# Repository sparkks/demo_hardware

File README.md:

# demo_hardware
Simple 78XX voltage regulator schematic and PCB board created using EAGLE 7.0.3
just temporary - for github testing purposes with schematic and PCB files

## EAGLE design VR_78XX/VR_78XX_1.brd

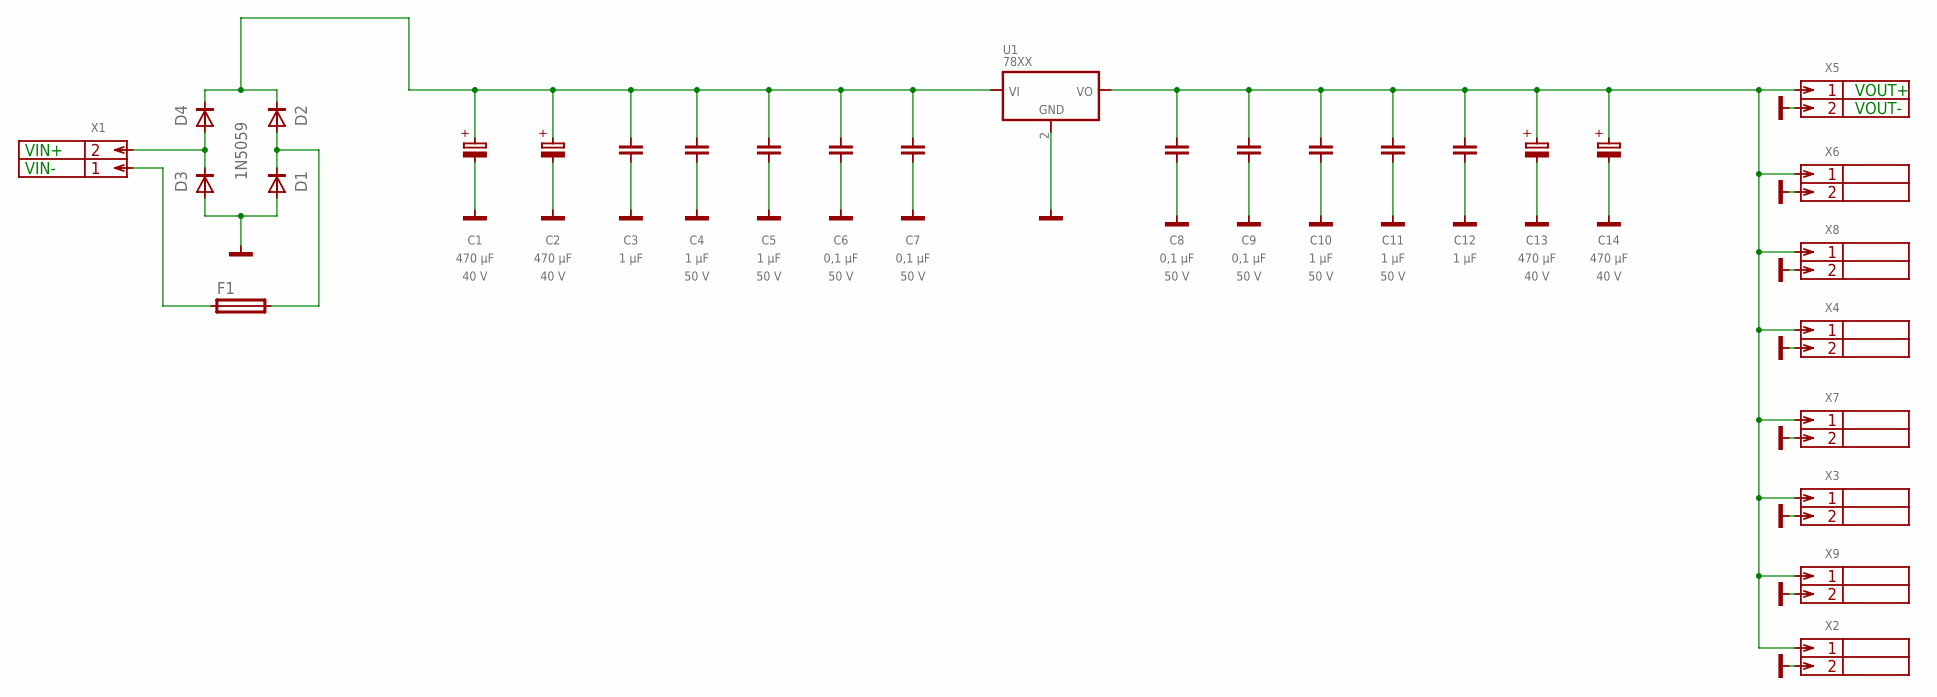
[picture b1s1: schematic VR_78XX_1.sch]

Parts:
C1, C2, C13, C14: 470 µF; AHT10-30C; VOLTAGE 40 V
C3, C12: 1 µF; 1
C4, C5, C10, C11: 1 µF; C050-025X075
C6, C7, C8, C9: 0,1 µF; C050-025X075
D1, D2, D3, D4: 1N5059; DO204-10
F1: GSH15
U1: 78XX; TO220H
X1: AK100V5; AK100-2V
X2, X3, X4, X5, X6, X7, X8, X9: MTA02-100; 10X02MTA

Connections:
GND: C1.-, C2.-, C3.2, C4.2, C5.2, C6.2, C7.2, C8.2, C9.2, C10.2, C11.2, C12.2, C13.-, C14.-, D1.A, D3.A, U1.2 (GND), X2.2, X3.2, X4.2, X5.2, X6.2, X7.2, X8.2, X9.2
unnamed: D3.C, D4.A, X1.P$2 (2)
unnamed: D1.C, D2.A, F1.2
unnamed: F1.1, X1.P$1 (1)
VIN+: C1.+, C2.+, C3.1, C4.1, C5.1, C6.1, C7.1, D2.C, D4.C, U1.1 (VI)
VOUT+: C8.1, C9.1, C10.1, C11.1, C12.1, C13.+, C14.+, U1.3 (VO), X2.1, X3.1, X4.1, X5.1, X6.1, X7.1, X8.1, X9.1

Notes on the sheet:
VIN+
VIN-
VOUT+
VOUT-

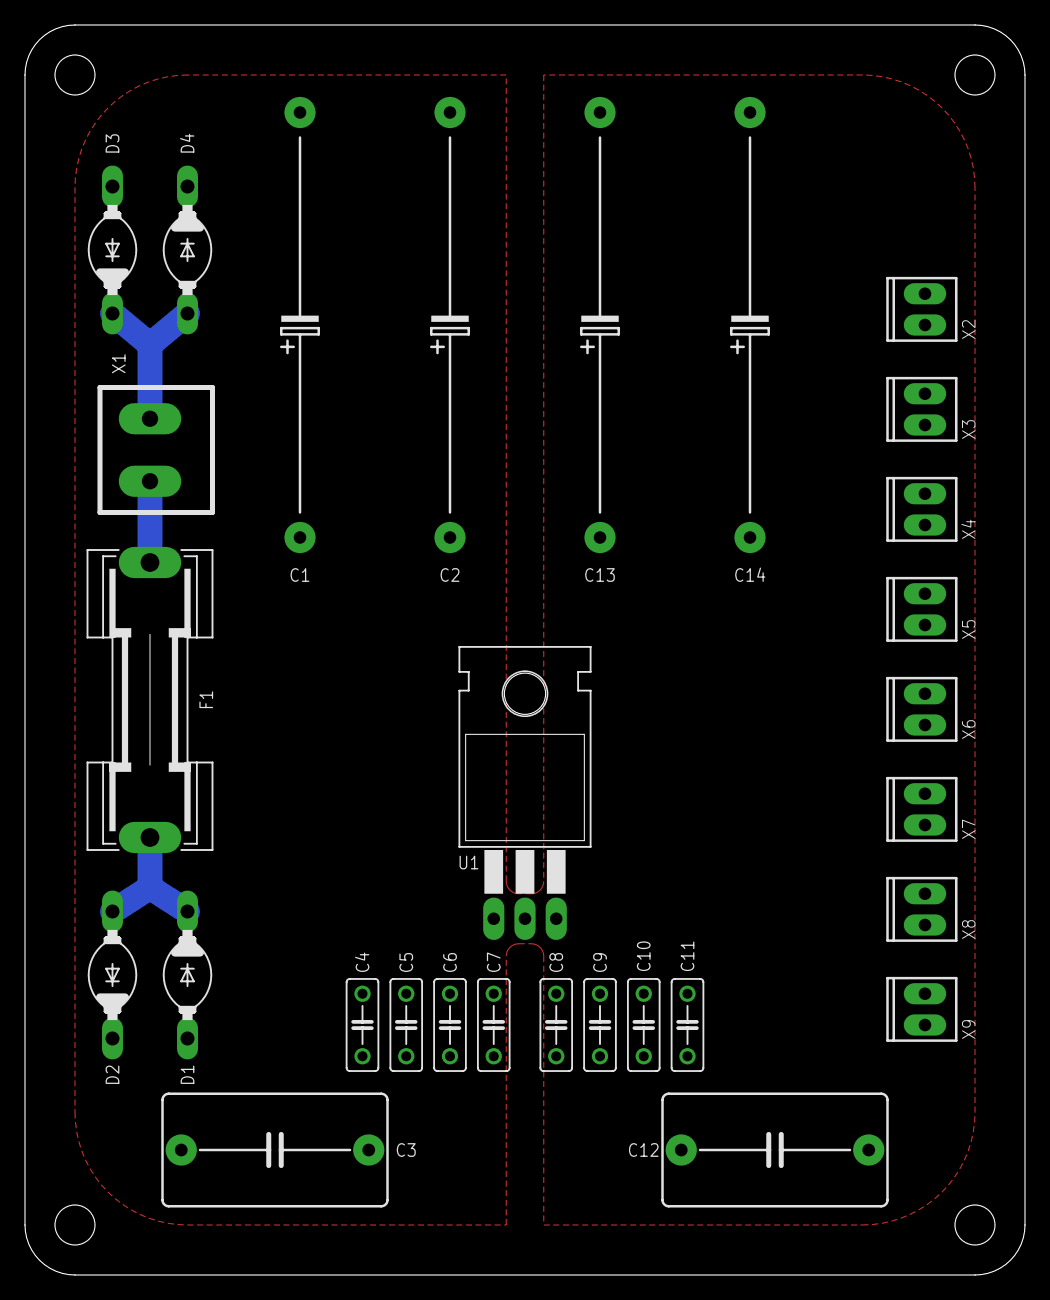
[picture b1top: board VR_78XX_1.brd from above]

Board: 2 copper layers, 80.0 x 100.0 mm, 34 parts (0 on the bottom side), 6 nets.

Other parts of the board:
U$1, U$2, U$3, U$4: KRASTAI3MM
U$6: 100X80PCB

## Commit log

2018-03-25 voltage regulator initial schematic and pcb files
2018-03-25 deleted film capacitors
2018-03-25 edited readme
2018-03-25 placed files to directory
2018-03-25 corection
2018-03-25 layout, caps
    cleaned layout a little bit, added ceramic bypass capacitors.
2018-03-25 layout, caps
    cleaned layout a little bit, added ceramic bypass caps.
2018-03-25 deleted unecessary temp files
2018-03-25 added more decoupling caps
    Added more decoupling caps
